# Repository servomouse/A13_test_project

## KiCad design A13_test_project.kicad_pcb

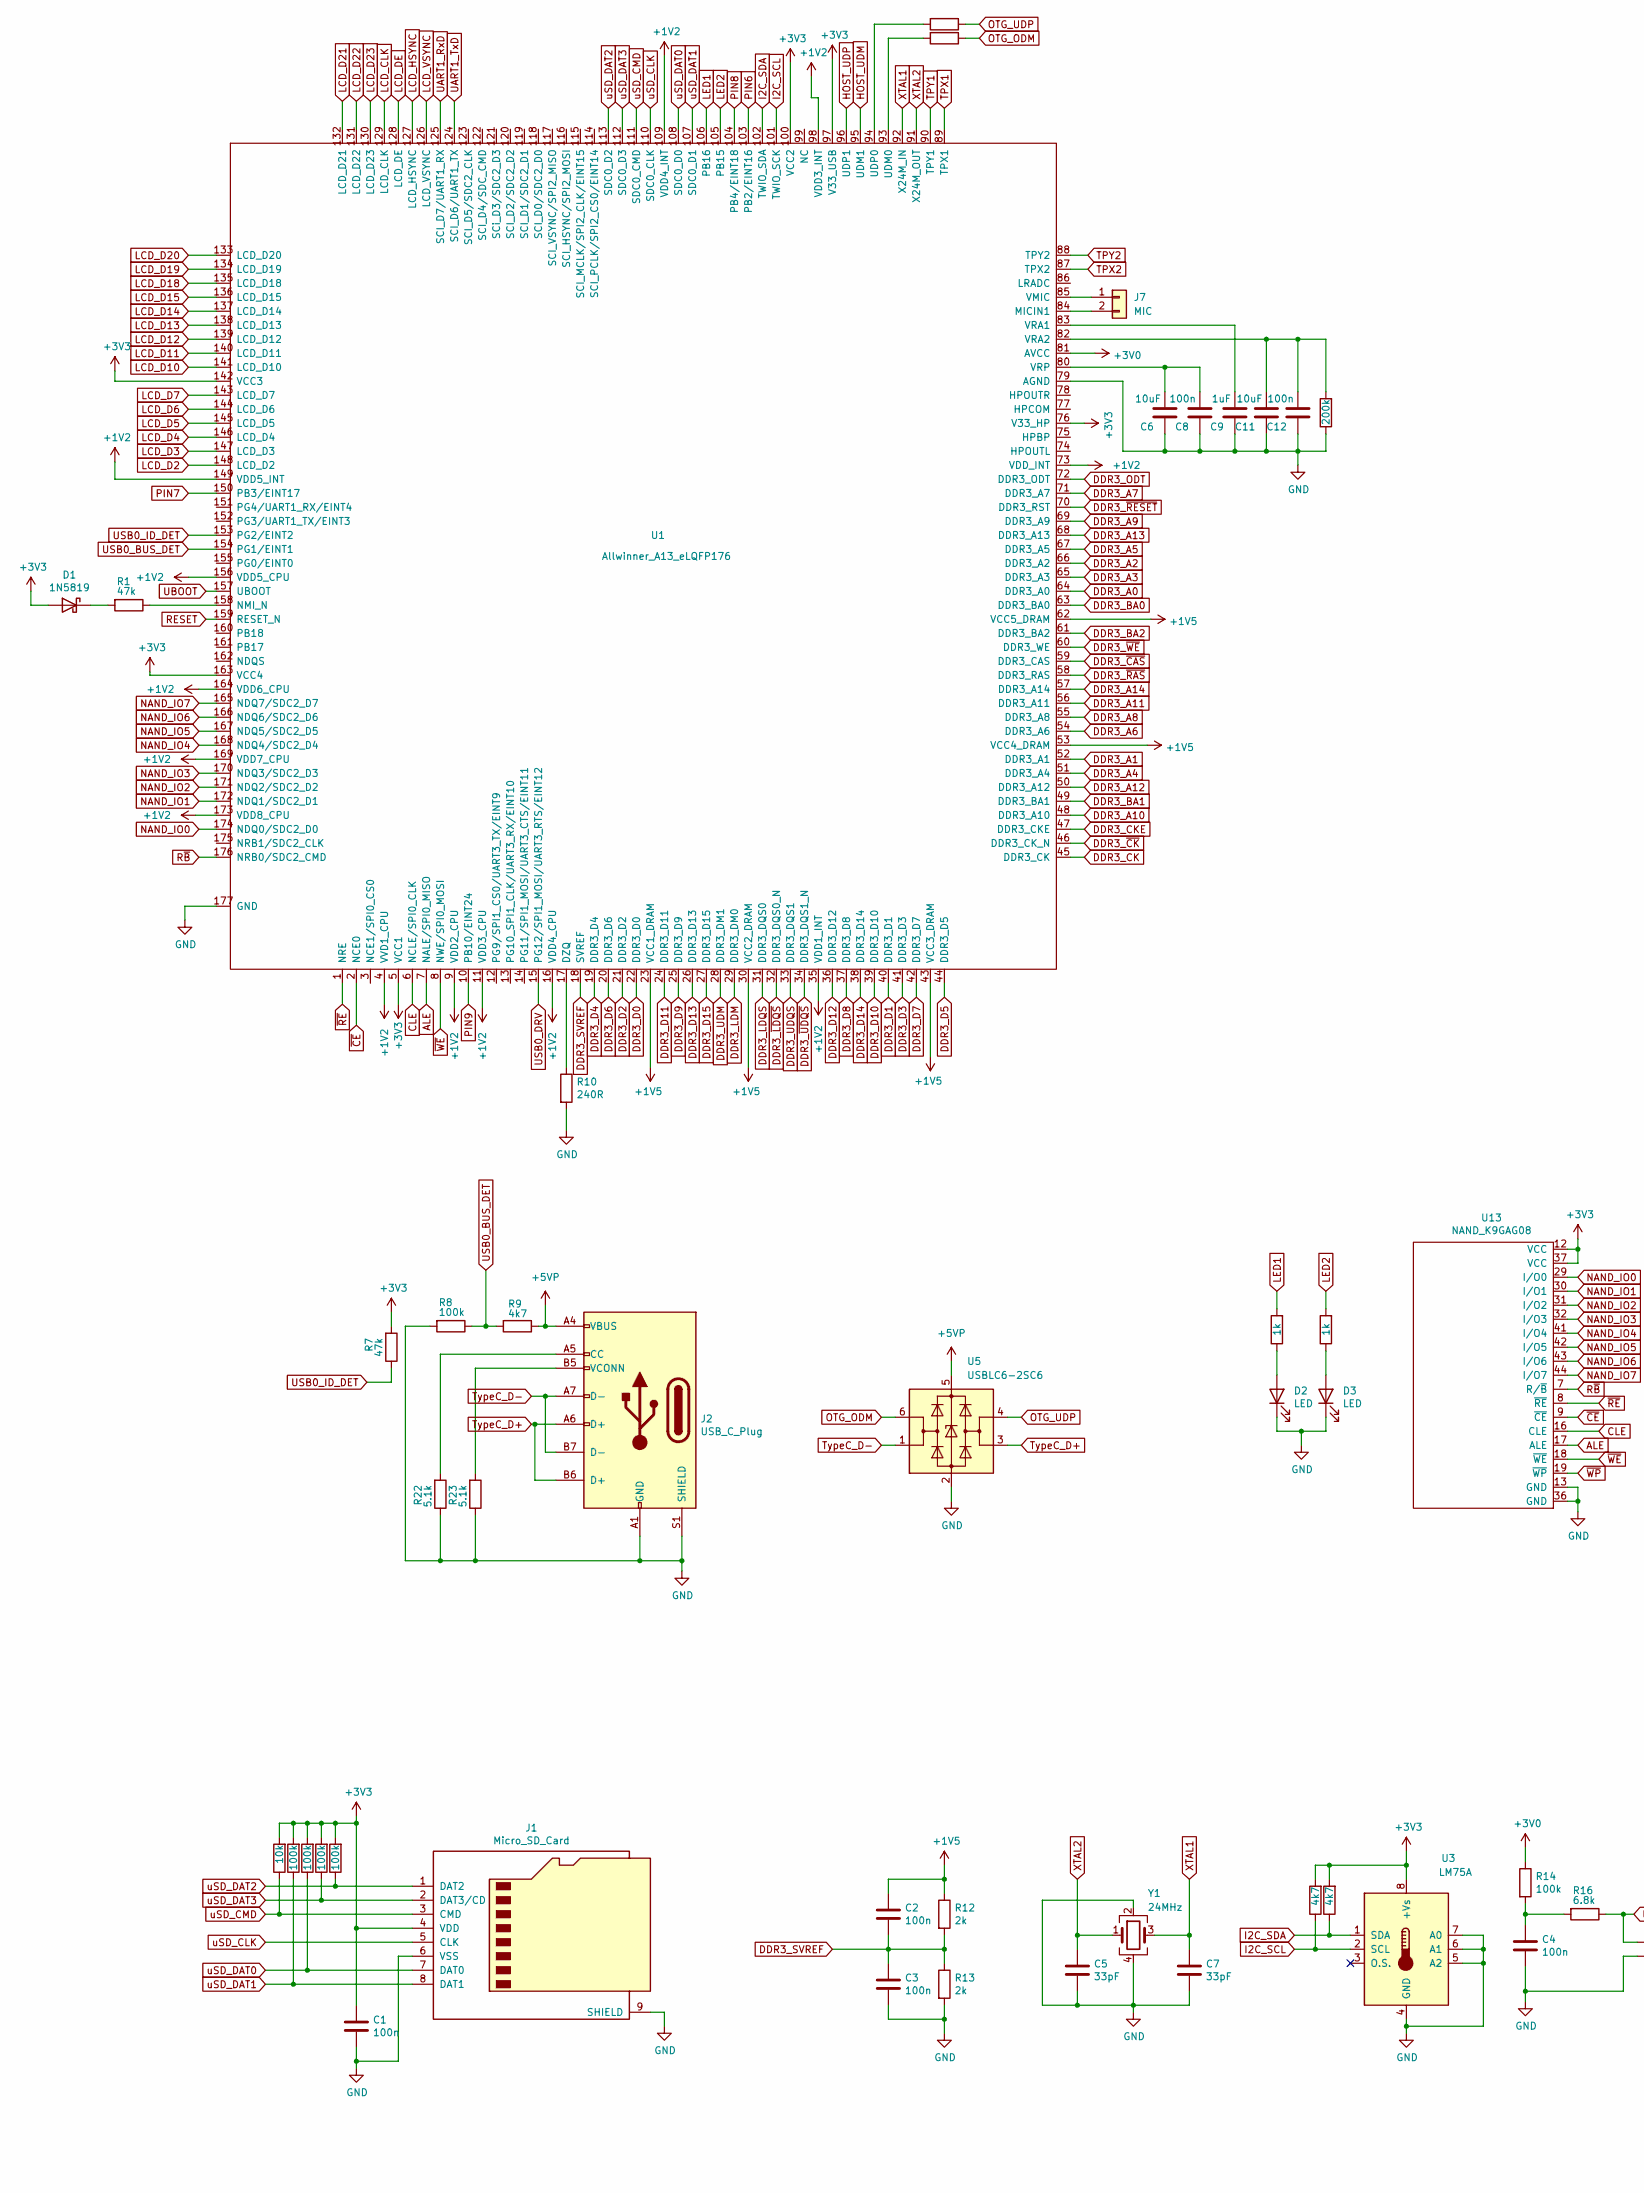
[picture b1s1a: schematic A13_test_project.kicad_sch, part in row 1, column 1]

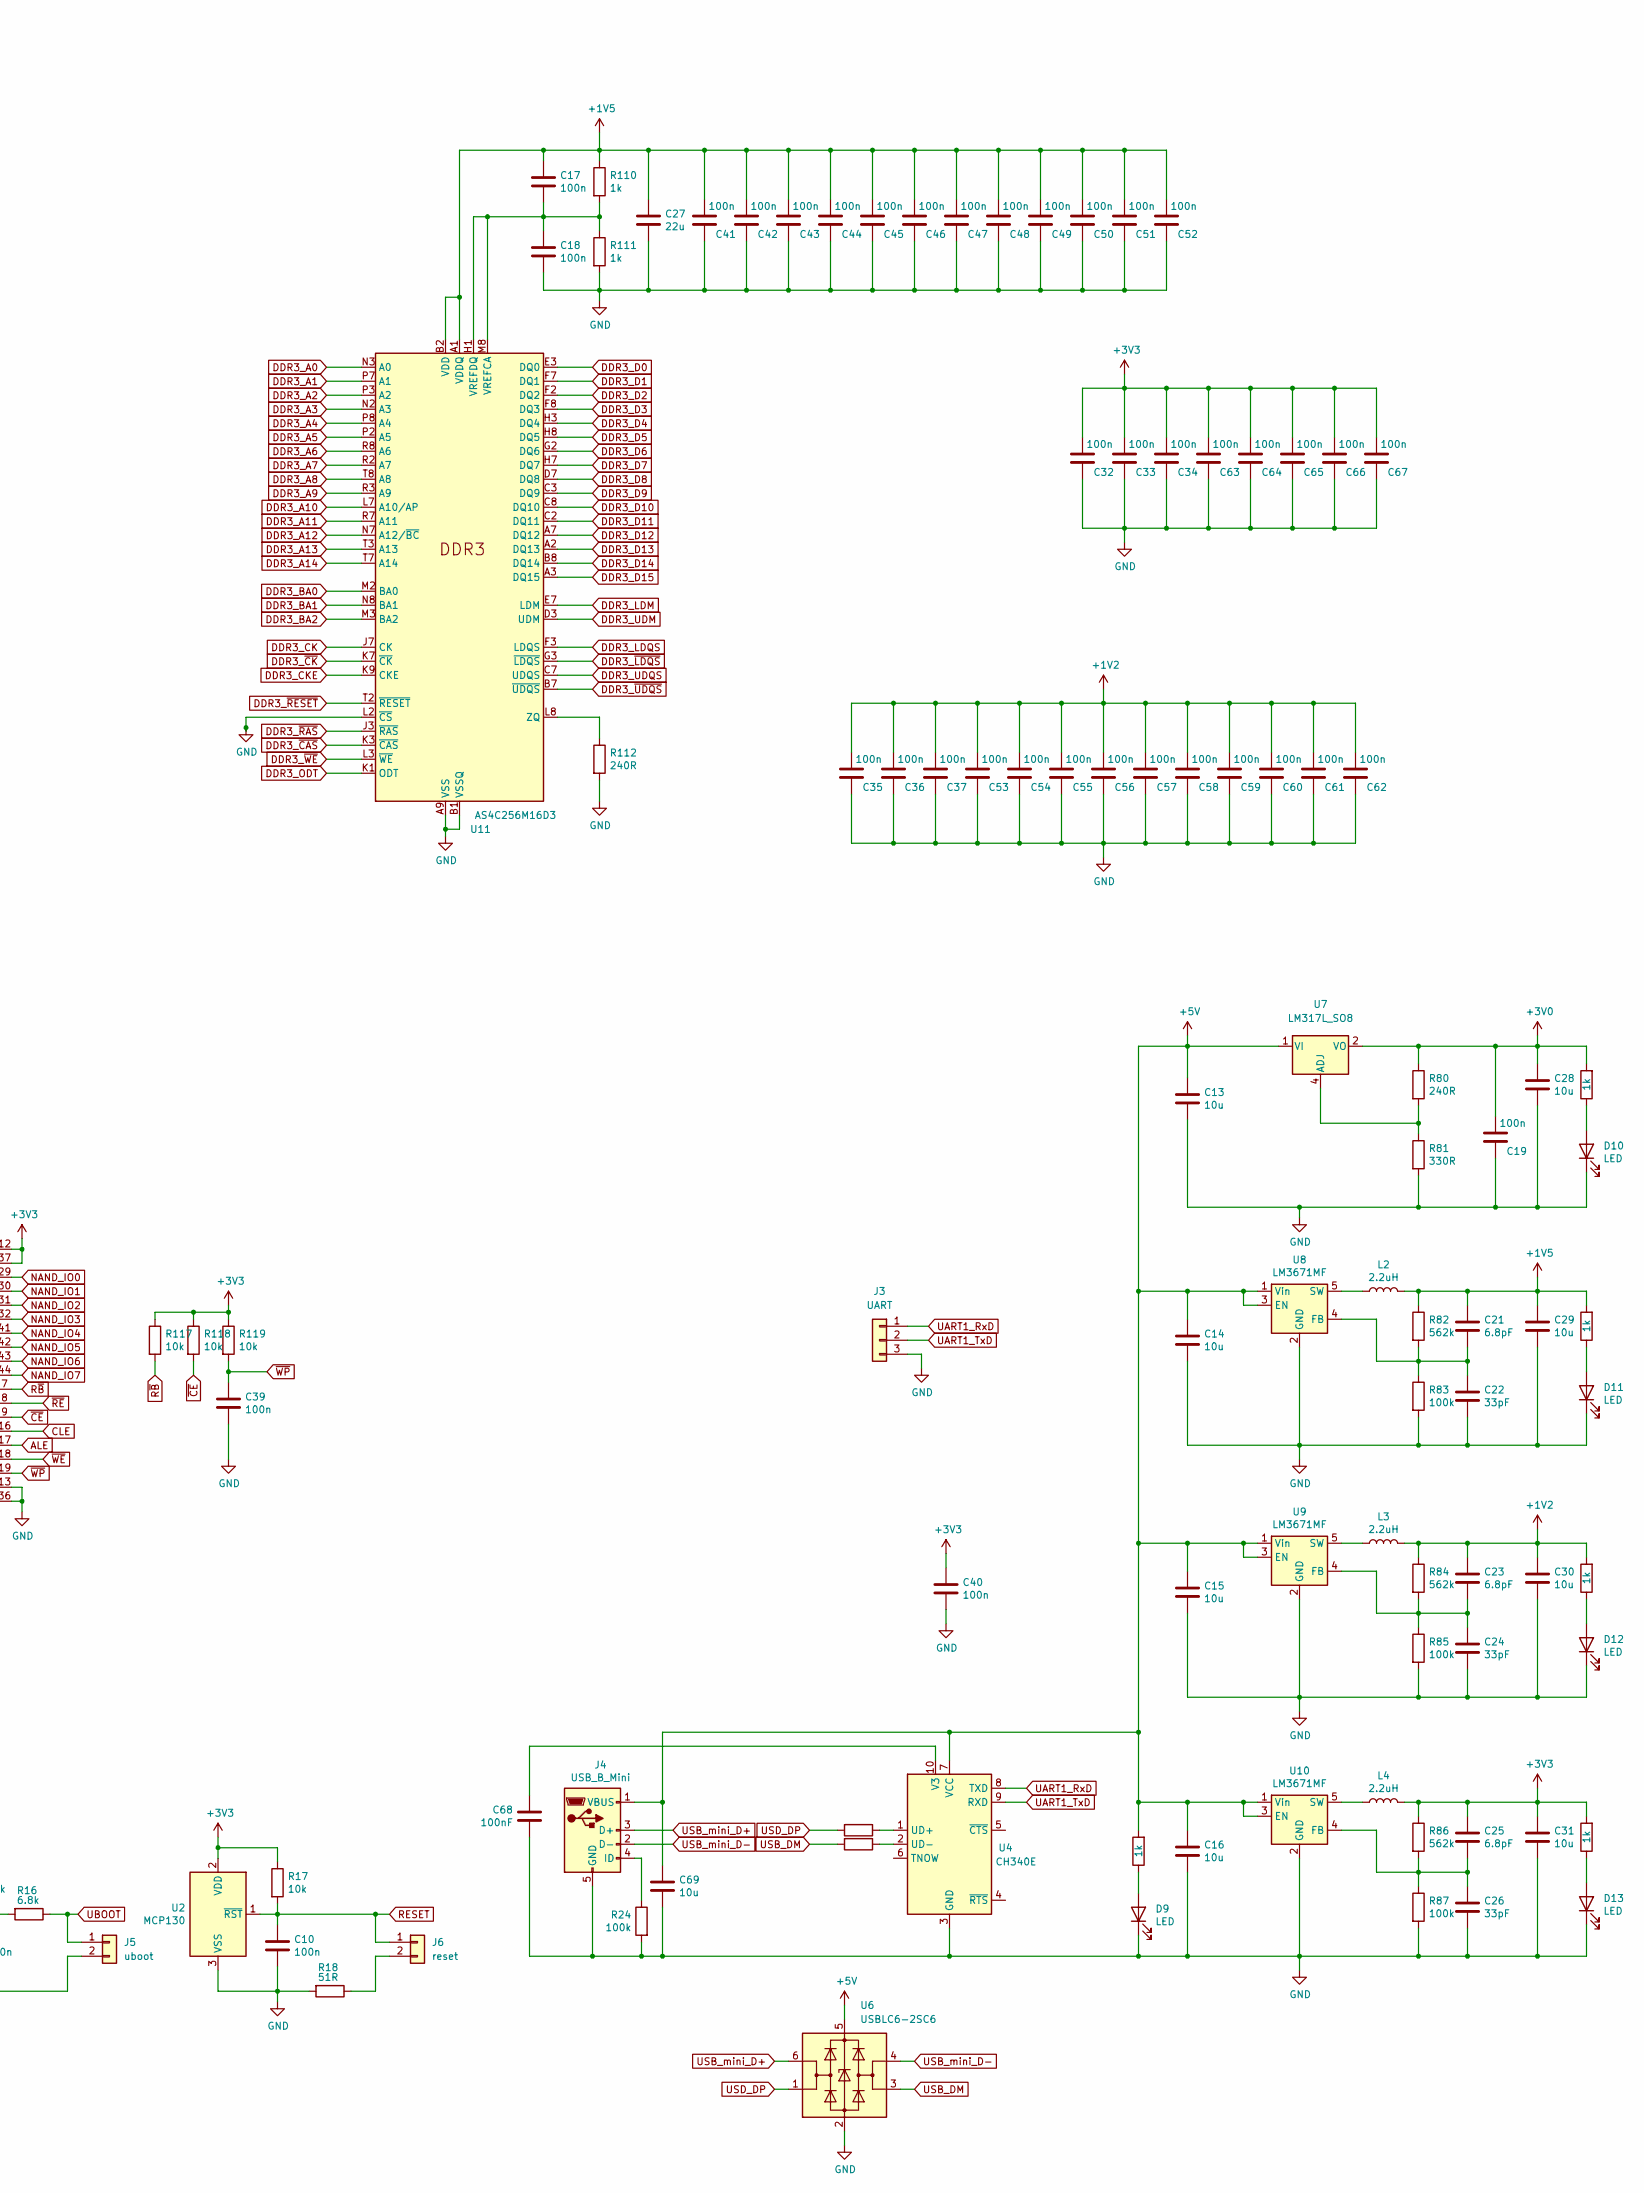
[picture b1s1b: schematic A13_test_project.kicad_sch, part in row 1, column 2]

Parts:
C1: 100n; C_0805_2012Metric
C2, C3, C4, C8, C10, C12, C17, C18, C32, C33, C34, C35, C36, C37, C39, C40, C41, C42, C43, C44, C45, C46, C47, C48, C49, C50, C51, C52, C53, C54, C55, C56, C57, C58, C59, C60, C61, C62, C63, C64, C65, C66, C67: 100n; C_0402_1005Metric
C5, C7, C22, C24, C26: 33pF; C_0402_1005Metric
C6, C11: 10uF; C_0402_1005Metric
C9: 1uF; C_0402_1005Metric
C13, C14, C15, C16, C28, C29, C30, C31, C69: 10u; C_0805_2012Metric
C19: 100n; C_0402
C21, C23, C25: 6.8pF; C_0402_1005Metric
C27: 22u; C_0805_2012Metric
C68: 100nF; C_0402_1005Metric
D1: 1N5819; D_SOD-323
D2, D3, D9, D10, D11, D12, D13: LED; LED_0603_1608Metric
J1: Micro_SD_Card; micro-sd
J2: USB_C_Plug; USB_C_Receptacle_HRO_TYPE-C-31-M-12
J3: UART; PinHeader_1x03_P2.54mm_Vertical
J4: USB_B_Mini; USB_Mini-B_Lumberg_2486_01_Horizontal
J5: uboot; PinHeader_1x02_P2.54mm
J6: reset; PinHeader_1x02_P2.54mm
J7: MIC; PinHeader_1x02_P2.54mm
L2, L3, L4: 2.2uH; L-CD32
R1, R7: 47k; R_0402_1005Metric
R2, R17, R117, R118, R119: 10k; R_0402_1005Metric
R3, R4, R5, R6, R8, R14, R24, R83, R85, R87: 100k; R_0402_1005Metric
R9, R19, R21: 4k7; R_0402_1005Metric
R10, R80, R112: 240R; R_0402_1005Metric
R11, R15, R52, R110, R111, R113, R114, R115, R116: 1k; R_0402_1005Metric
R12, R13: 2k; R_0402_1005Metric
R16: 6.8k; R_0402_1005Metric
R18: 51R; R_0402_1005Metric
R20: 200k; R_0402_1005Metric
R22, R23: 5.1k; R_0402_1005Metric
R25, R26, R27, R28: 22R; R_0402_1005Metric
R81: 330R; R_0402_1005Metric
R82, R84, R86: 562k; R_0402_1005Metric
U1: Allwinner_A13_eLQFP176; LQFP-176_20x20mm_P0.4mm
U2: MCP130; TO-92_Inline
U3: LM75A; SO-8_3.9x4.9mm_P1.27mm
U4: CH340E; MSOP-10_3x3mm_P0.5mm
U5, U6: USBLC6-2SC6; SOT-23-6
U7: LM317L_SO8; SOIC-8_3.9x4.9mm_P1.27mm
U8, U9, U10: LM3671MF; TSOT-23-5
U11: AS4C256M16D3; BGA-96_9.0x13.0mm_Layout2x3x16_P0.8mm
U13: NAND_K9GAG08; TSOP-48(TYPE1)
Y1: 24MHz; Crystal_SMD_2016-4Pin_2.0x1.6mm

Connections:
+1V5: C2.1, C17.1, C21.1, C27.1, C29.1, C41.2, C42.2, C43.2, C44.2, C45.2, C46.2, C47.2, C48.2, C49.2, C50.2, C51.2, C52.2, L2.2, R12.1, R82.1, R110.1, R114.2, U1.23 (VCC1_DRAM), U1.30 (VCC2_DRAM), U1.43 (VCC3_DRAM), U1.53 (VCC4_DRAM), U1.62 (VCC5_DRAM), U11.A1 (VDDQ), U11.A8 (VDDQ), U11.B2 (VDD), U11.C1 (VDDQ), U11.C9 (VDDQ), U11.D2 (VDDQ), U11.D9 (VDD), U11.E9 (VDDQ), U11.F1 (VDDQ), U11.G7 (VDD), U11.H2 (VDDQ), U11.H9 (VDDQ), U11.K2 (VDD), U11.K8 (VDD), U11.N1 (VDD), U11.N9 (VDD), U11.R1 (VDD), U11.R9 (VDD)
+3V0: C19.2, C28.1, R14.1, R80.1, R113.2, U1.81 (AVCC), U7.2 (VO), U7.3 (VO), U7.6 (VO), U7.7 (VO)
+5V: C13.1, C14.1, C15.1, C16.1, C69.1, J4.1 (VBUS), R52.2, U4.7 (VCC), U6.5 (VBUS), U7.1 (VI), U8.1 (Vin), U8.3 (EN), U9.1 (Vin), U9.3 (EN), U10.1 (Vin), U10.3 (EN)
+5VP: J2.A4 (VBUS), J2.A9 (VBUS), J2.B4 (VBUS), J2.B9 (VBUS), R9.1, U5.5 (VBUS)
ALE: U1.7 (NALE/SPI0_MISO), U13.17 (ALE)
CLE: U1.6 (NCLE/SPI0_CLK), U13.16 (CLE)
DDR3_A0: U1.64 (DDR3_A0), U11.N3 (A0)
DDR3_A1: U1.52 (DDR3_A1), U11.P7 (A1)
DDR3_A2: U1.66 (DDR3_A2), U11.P3 (A2)
DDR3_A3: U1.65 (DDR3_A3), U11.N2 (A3)
DDR3_A4: U1.51 (DDR3_A4), U11.P8 (A4)
DDR3_A5: U1.67 (DDR3_A5), U11.P2 (A5)
DDR3_A6: U1.54 (DDR3_A6), U11.R8 (A6)
DDR3_A7: U1.71 (DDR3_A7), U11.R2 (A7)
DDR3_A8: U1.55 (DDR3_A8), U11.T8 (A8)
DDR3_A9: U1.69 (DDR3_A9), U11.R3 (A9)
DDR3_A10: U1.48 (DDR3_A10), U11.L7 (A10/AP)
DDR3_A11: U1.56 (DDR3_A11), U11.R7 (A11)
DDR3_A12: U1.50 (DDR3_A12), U11.N7 (A12/~BC)
DDR3_A13: U1.68 (DDR3_A13), U11.T3 (A13)
DDR3_A14: U1.57 (DDR3_A14), U11.T7 (A14)
DDR3_BA0: U1.63 (DDR3_BA0), U11.M2 (BA0)
DDR3_BA1: U1.49 (DDR3_BA1), U11.N8 (BA1)
DDR3_BA2: U1.61 (DDR3_BA2), U11.M3 (BA2)
DDR3_CK: U1.45 (DDR3_CK), U11.J7 (CK)
DDR3_CKE: U1.47 (DDR3_CKE), U11.K9 (CKE)
DDR3_D0: U1.22 (DDR3_D0), U11.E3 (DQ0)
DDR3_D1: U1.40 (DDR3_D1), U11.F7 (DQ1)
DDR3_D2: U1.21 (DDR3_D2), U11.F2 (DQ2)
DDR3_D3: U1.41 (DDR3_D3), U11.F8 (DQ3)
DDR3_D4: U1.19 (DDR3_D4), U11.H3 (DQ4)
DDR3_D5: U1.44 (DDR3_D5), U11.H8 (DQ5)
DDR3_D6: U1.20 (DDR3_D6), U11.G2 (DQ6)
DDR3_D7: U1.42 (DDR3_D7), U11.H7 (DQ7)
DDR3_D8: U1.37 (DDR3_D8), U11.D7 (DQ8)
DDR3_D9: U1.25 (DDR3_D9), U11.C3 (DQ9)
DDR3_D10: U1.39 (DDR3_D10), U11.C8 (DQ10)
DDR3_D11: U1.24 (DDR3_D11), U11.C2 (DQ11)
DDR3_D12: U1.36 (DDR3_D12), U11.A7 (DQ12)
DDR3_D13: U1.26 (DDR3_D13), U11.A2 (DQ13)
DDR3_D14: U1.38 (DDR3_D14), U11.B8 (DQ14)
DDR3_D15: U1.27 (DDR3_D15), U11.A3 (DQ15)
DDR3_LDM: U1.29 (DDR3_DM0), U11.E7 (LDM)
DDR3_LDQS: U1.31 (DDR3_DQS0), U11.F3 (LDQS)
DDR3_ODT: U1.72 (DDR3_ODT), U11.K1 (ODT)
DDR3_SVREF: C2.2, C3.1, R12.2, R13.1, U1.18 (SVREF)
DDR3_UDM: U1.28 (DDR3_DM1), U11.D3 (UDM)
DDR3_UDQS: U1.33 (DDR3_DQS1), U11.C7 (UDQS)
DDR3_~CAS: U1.59 (DDR3_CAS), U11.K3 (~CAS)
DDR3_~CK: U1.46 (DDR3_CK_N), U11.K7 (~CK)
DDR3_~LDQS: U1.32 (DDR3_DQS0_N), U11.G3 (~LDQS)
DDR3_~RAS: U1.58 (DDR3_RAS), U11.J3 (~RAS)
DDR3_~RESET: U1.70 (DDR3_RST), U11.T2 (~RESET)
DDR3_~UDQS: U1.34 (DDR3_DQS1_N), U11.B7 (~UDQS)
DDR3_~WE: U1.60 (DDR3_WE), U11.L3 (~WE)
HOST_UDM: U1.95 (UDM1)
HOST_UDP: U1.96 (UDP1)
I2C_SCL: R19.1, U1.101 (TWIO_SCK), U3.2 (SCL)
I2C_SDA: R21.1, U1.102 (TWIO_SDA), U3.1 (SDA)
LCD_CLK: U1.129 (LCD_CLK)
LCD_D2: U1.148 (LCD_D2)
LCD_D3: U1.147 (LCD_D3)
LCD_D4: U1.146 (LCD_D4)
LCD_D5: U1.145 (LCD_D5)
LCD_D6: U1.144 (LCD_D6)
LCD_D7: U1.143 (LCD_D7)
LCD_D10: U1.141 (LCD_D10)
LCD_D11: U1.140 (LCD_D11)
LCD_D12: U1.139 (LCD_D12)
LCD_D13: U1.138 (LCD_D13)
LCD_D14: U1.137 (LCD_D14)
LCD_D15: U1.136 (LCD_D15)
LCD_D18: U1.135 (LCD_D18)
LCD_D19: U1.134 (LCD_D19)
LCD_D20: U1.133 (LCD_D20)
LCD_D21: U1.132 (LCD_D21)
LCD_D22: U1.131 (LCD_D22)
LCD_D23: U1.130 (LCD_D23)
LCD_DE: U1.128 (LCD_DE)
LCD_HSYNC: U1.127 (LCD_HSYNC)
LCD_VSYNC: U1.126 (LCD_VSYNC)
LED1: R11.2, U1.106 (PB16)
LED2: R15.2, U1.105 (PB15)
NAND_IO0: U1.174 (NDQ0/SDC2_D0), U13.29 (I/O0)
NAND_IO1: U1.172 (NDQ1/SDC2_D1), U13.30 (I/O1)
NAND_IO2: U1.171 (NDQ2/SDC2_D2), U13.31 (I/O2)
NAND_IO3: U1.170 (NDQ3/SDC2_D3), U13.32 (I/O3)
NAND_IO4: U1.168 (NDQ4/SDC2_D4), U13.41 (I/O4)
NAND_IO5: U1.167 (NDQ5/SDC2_D5), U13.42 (I/O5)
NAND_IO6: U1.166 (NDQ6/SDC2_D6), U13.43 (I/O6)
NAND_IO7: U1.165 (NDQ7/SDC2_D7), U13.44 (I/O7)
unnamed: C4.1, R14.2, R16.2
unnamed: C6.2, C8.2, U1.80 (VRP)
unnamed: C9.2, U1.83 (VRA1)
unnamed: C11.2, C12.2, R20.2, U1.82 (VRA2)
unnamed: C17.2, C18.1, R110.2, R111.1, U11.H1 (VREFDQ), U11.M8 (VREFCA)
unnamed: C21.2, C22.1, R82.2, R83.1, U8.4 (FB)
unnamed: C23.2, C24.1, R84.2, R85.1, U9.4 (FB)
unnamed: C25.2, C26.1, R86.2, R87.1, U10.4 (FB)
unnamed: C68.1, U4.10 (V3)
unnamed: D1.1 (K), R1.2
unnamed: D2.2 (A), R11.1
unnamed: D3.2 (A), R15.1
unnamed: D9.2 (A), R52.1
unnamed: D10.2 (A), R113.1
unnamed: D11.2 (A), R114.1
unnamed: D12.2 (A), R115.1
unnamed: D13.2 (A), R116.1
unnamed: J2.A5 (CC), R22.2
unnamed: J2.B5 (VCONN), R23.2
unnamed: J4.4 (ID), R24.1
unnamed: J6.2, R18.1
unnamed: L2.1, U8.5 (SW)
unnamed: L3.1, U9.5 (SW)
unnamed: L4.1, U10.5 (SW)
unnamed: R1.1, U1.158 (NMI_N)
unnamed: R10.1, U1.17 (DZQ)
unnamed: R25.2, U1.94 (UDP0)
unnamed: R26.2, U1.93 (UDM0)
unnamed: R27.1, U4.1 (UD+)
unnamed: R28.1, U4.2 (UD-)
unnamed: R80.2, R81.1, U7.4 (ADJ)
unnamed: R112.1, U11.L8 (ZQ)
unnamed: J7.2, U1.84 (MICIN1)
unnamed: J7.1, U1.85 (VMIC)
OTG_ODM: R26.1, U5.6 (I/O1)
OTG_UDP: R25.1, U5.4 (I/O2)
PIN6: U1.103 (PB2/EINT16)
PIN7: U1.150 (PB3/EINT17)
PIN8: U1.104 (PB4/EINT18)
PIN9: U1.10 (PB10/EINT24)
RESET: C10.1, J6.1, R17.2, U1.159 (RESET_N), U2.1 (~RST)
R~B: R117.2, U1.176 (NRB0/SDC2_CMD), U13.7 (R/~B)
TypeC_D+: J2.A6 (D+), J2.B6 (D+), U5.3 (I/O2)
TypeC_D-: J2.A7 (D-), J2.B7 (D-), U5.1 (I/O1)
UART1_RxD: J3.1, U1.125 (SCI_D7/UART1_RX), U4.8 (TXD)
UART1_TxD: J3.2, U1.124 (SCI_D6/UART1_TX), U4.9 (RXD)
UBOOT: J5.1, R16.1, U1.157 (UBOOT)
USB0_BUS_DET: R8.1, R9.2, U1.154 (PG1/EINT1)
USB0_DRV: U1.15 (PG12/SPI1_MOSI/UART3_RTS/EINT12)
USB0_ID_DET: R7.1, U1.153 (PG2/EINT2)
USB_DM: R28.2, U6.3 (I/O2)
USB_mini_D+: J4.3 (D+), U6.6 (I/O1)
USB_mini_D-: J4.2 (D-), U6.4 (I/O2)
USD_DP: R27.2, U6.1 (I/O1)
XTAL1: C7.1, U1.92 (X24M_IN), Y1.3
XTAL2: C5.1, U1.91 (X24M_OUT), Y1.1
uSD_CLK: J1.5 (CLK), U1.110 (SDC0_CLK)
uSD_CMD: J1.3 (CMD), R2.1, U1.111 (SDC0_CMD)
uSD_DAT0: J1.7 (DAT0), R4.1, U1.108 (SDC0_D0)
uSD_DAT1: J1.8 (DAT1), R3.1, U1.107 (SDC0_D1)
uSD_DAT2: J1.1 (DAT2), R6.1, U1.113 (SDC0_D2)
uSD_DAT3: J1.2 (DAT3/CD), R5.1, U1.112 (SDC0_D3)
~CE: R118.2, U1.2 (NCE0), U13.9 (~CE)
~RE: U1.1 (NRE), U13.8 (~RE)
~WE: U1.8 (NWE/SPI0_MOSI), U13.18 (~WE)
~WP: C39.1, R119.2, U13.19 (~WP)

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
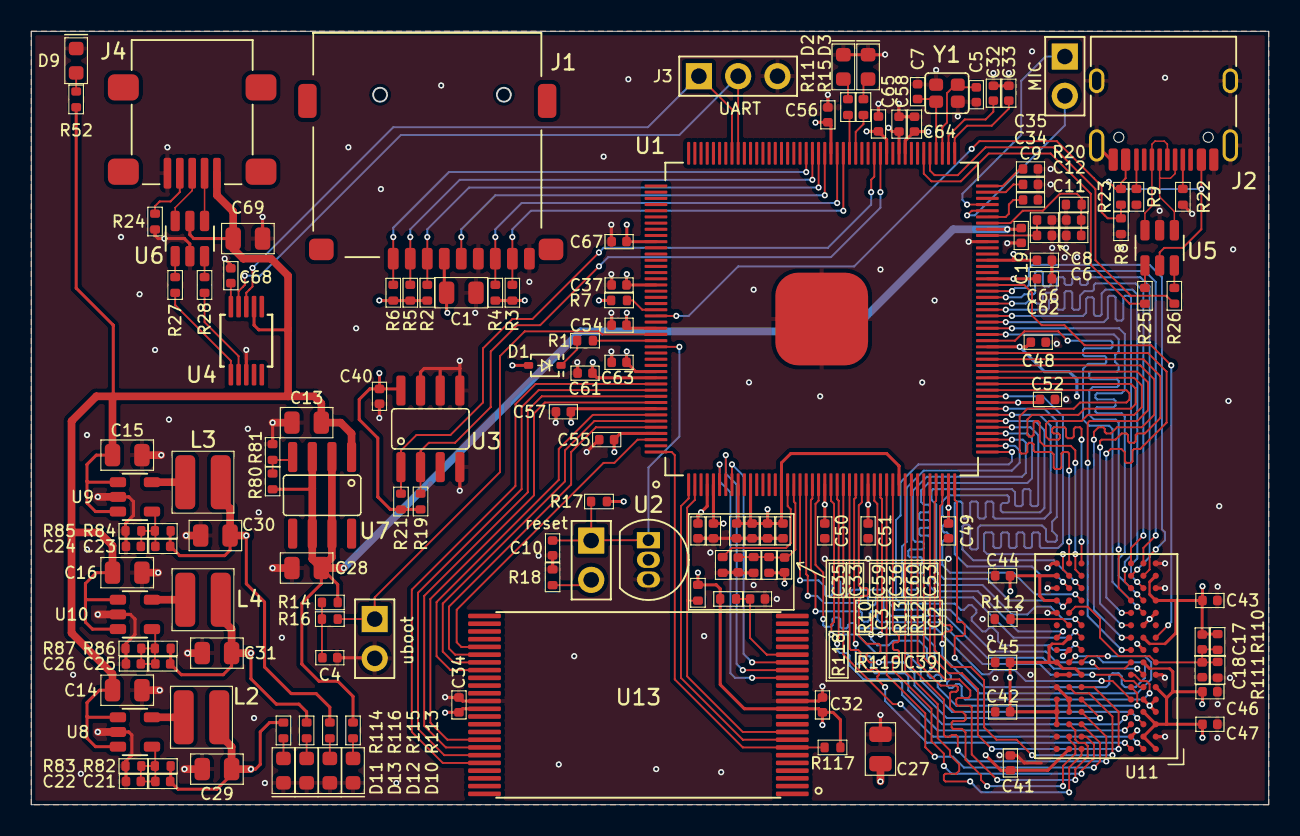
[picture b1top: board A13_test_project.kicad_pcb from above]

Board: 4 copper layers, 79.9 x 49.9 mm, 149 parts (0 on the bottom side), 135 nets.

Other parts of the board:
C32#2, C33#2, C34#2, C35#2: 100n; C_0402

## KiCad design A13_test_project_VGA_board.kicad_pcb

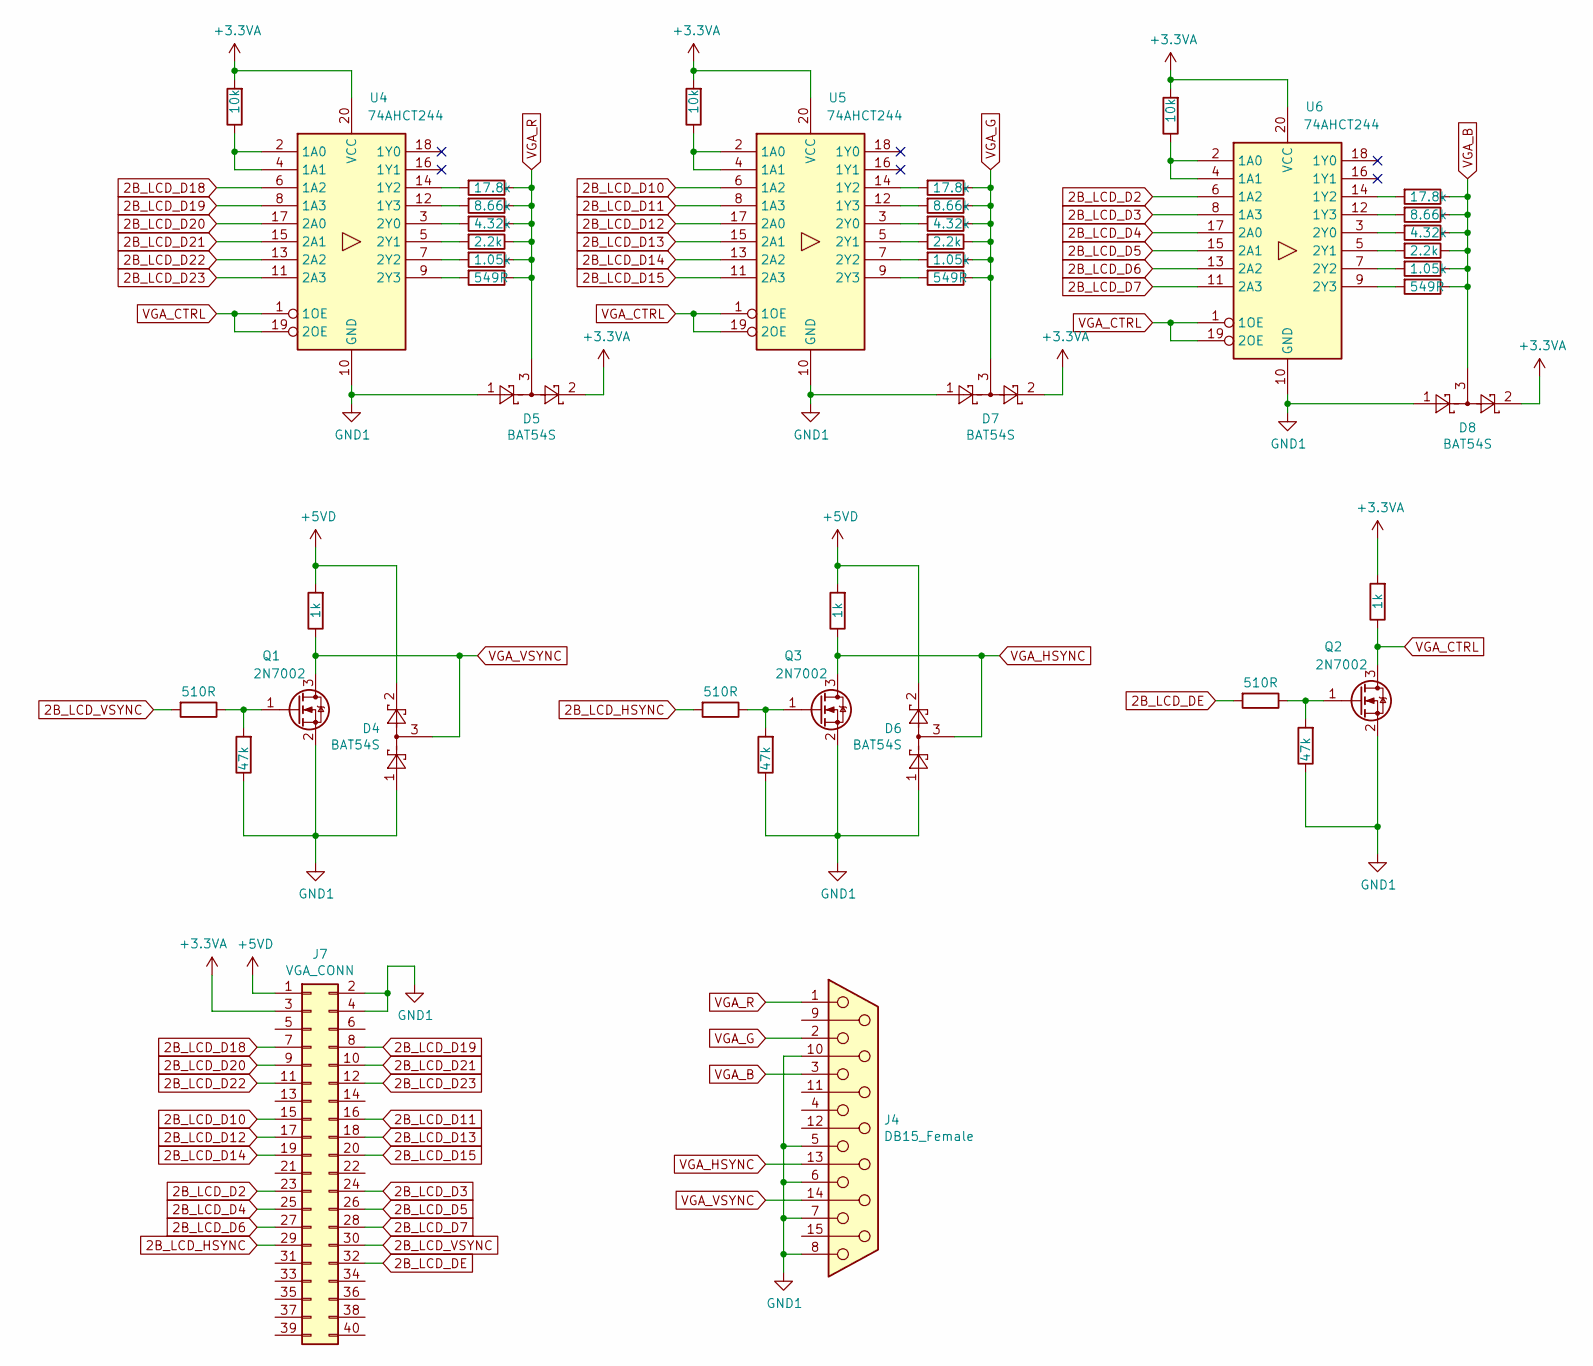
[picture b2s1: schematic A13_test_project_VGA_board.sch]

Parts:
D4, D5, D6, D7, D8: BAT54S; SOT-23
J4: DB15_Female; DSUB-15-HD_Female_Horizontal_P2.29x1.98mm_EdgePinOffset3.03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
J7: VGA_CONN; PinSocket_2x20_P2.54mm_Vertical
Q1, Q2, Q3: 2N7002; SOT-23
R22, R23, R36: 510R; R_0402_1005Metric
R24, R35, R45: 10k; R_0402_1005Metric
R25, R26, R37: 47k; R_0402_1005Metric
R27, R28, R38: 1k; R_0402_1005Metric
R29, R39, R46: 17.8k; R_0402_1005Metric
R30, R40, R47: 8.66k; R_0402_1005Metric
R31, R41, R48: 4.32k; R_0402_1005Metric
R32, R42, R49: 2.2k; R_0402_1005Metric
R33, R43, R50: 1.05k; R_0402_1005Metric
R34, R44, R51: 549R; R_0402_1005Metric
U4, U5, U6: 74AHCT244; SO-20_5.3x12.6mm_P1.27mm

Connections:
2B_LCD_D2: J7.23, U6.6 (1A2)
2B_LCD_D3: J7.24, U6.8 (1A3)
2B_LCD_D4: J7.25, U6.17 (2A0)
2B_LCD_D5: J7.26, U6.15 (2A1)
2B_LCD_D6: J7.27, U6.13 (2A2)
2B_LCD_D7: J7.28, U6.11 (2A3)
2B_LCD_D10: J7.15, U5.6 (1A2)
2B_LCD_D11: J7.16, U5.8 (1A3)
2B_LCD_D12: J7.17, U5.17 (2A0)
2B_LCD_D13: J7.18, U5.15 (2A1)
2B_LCD_D14: J7.19, U5.13 (2A2)
2B_LCD_D15: J7.20, U5.11 (2A3)
2B_LCD_D18: J7.7, U4.6 (1A2)
2B_LCD_D19: J7.8, U4.8 (1A3)
2B_LCD_D20: J7.9, U4.17 (2A0)
2B_LCD_D21: J7.10, U4.15 (2A1)
2B_LCD_D22: J7.11, U4.13 (2A2)
2B_LCD_D23: J7.12, U4.11 (2A3)
2B_LCD_DE: J7.32, R23.2
2B_LCD_HSYNC: J7.29, R36.2
2B_LCD_VSYNC: J7.30, R22.2
+3.3VA: D5.2, D7.2, D8.2, J7.3, R24.2, R28.2, R35.2, R45.2, U4.20 (VCC), U5.20 (VCC), U6.20 (VCC)
+5VD: D4.2, D6.2, J7.1, R27.2, R38.2
GND1: D4.1, D5.1, D6.1, D7.1, D8.1, J4.5, J4.6, J4.7, J4.8, J4.10, J7.2, J7.4, Q1.2 (S), Q2.2 (S), Q3.2 (S), R25.1, R26.1, R37.1, U4.10 (GND), U5.10 (GND), U6.10 (GND)
unnamed: Q1.1 (G), R22.1, R25.2
unnamed: Q2.1 (G), R23.1, R26.2
unnamed: Q3.1 (G), R36.1, R37.2
unnamed: R24.1, U4.2 (1A0), U4.4 (1A1)
unnamed: R29.2, U4.14 (1Y2)
unnamed: R30.2, U4.12 (1Y3)
unnamed: R31.2, U4.3 (2Y0)
unnamed: R32.2, U4.5 (2Y1)
unnamed: R33.2, U4.7 (2Y2)
unnamed: R34.2, U4.9 (2Y3)
unnamed: R35.1, U5.2 (1A0), U5.4 (1A1)
unnamed: R39.2, U5.14 (1Y2)
unnamed: R40.2, U5.12 (1Y3)
unnamed: R41.2, U5.3 (2Y0)
unnamed: R42.2, U5.5 (2Y1)
unnamed: R43.2, U5.7 (2Y2)
unnamed: R44.2, U5.9 (2Y3)
unnamed: R45.1, U6.2 (1A0), U6.4 (1A1)
unnamed: R46.2, U6.14 (1Y2)
unnamed: R47.2, U6.12 (1Y3)
unnamed: R48.2, U6.3 (2Y0)
unnamed: R49.2, U6.5 (2Y1)
unnamed: R50.2, U6.7 (2Y2)
unnamed: R51.2, U6.9 (2Y3)
VGA_B: D8.3, J4.3, R46.1, R47.1, R48.1, R49.1, R50.1, R51.1
VGA_CTRL: Q2.3 (D), R28.1, U4.1 (1OE), U4.19 (2OE), U5.1 (1OE), U5.19 (2OE), U6.1 (1OE), U6.19 (2OE)
VGA_G: D7.3, J4.2, R39.1, R40.1, R41.1, R42.1, R43.1, R44.1
VGA_HSYNC: D6.3, J4.13, Q3.3 (D), R38.1
VGA_R: D5.3, J4.1, R29.1, R30.1, R31.1, R32.1, R33.1, R34.1
VGA_VSYNC: D4.3, J4.14, Q1.3 (D), R27.1

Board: 4 copper layers, 43 parts (0 on the bottom side), 54 nets, no tracks yet.

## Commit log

2022-06-01 Files have been sent to the factory
